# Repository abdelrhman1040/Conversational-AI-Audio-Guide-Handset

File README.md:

# Conversational-AI-Audio-Guide-Handset

ESP32-C5-based handset for a museum AI audio guide. Captures and cleans visitor speech, streams it over Wi-Fi to an edge AI server, and plays back the synthesized reply.

## Highlights

- ESP32-C5 compute/connectivity platform dual-band (2.4/5 GHz) Wi-Fi 6.
- Codec-integrated DSP for echo cancellation, noise suppression, and VAD.
- Dual-input charging: Auto-arbitrated dual-input charging (Pogo pins + USB-C).
- 12-hour runtime on a single 1S Li-Po cell.
- BOM cost-modeled for 50, 100, and 500 units.
- AI inference is handled entirely by the edge server.

## Schematic & PCB

### Schematics

*Page 1: Top-Level Hierarchy.*

*Page 2: Power & Battery Management.*

*Page 3: Microcontroller & User Interface.*

*Page 4: Audio System.*

---

### PCB Layout

## Power Subsystem

| Component | Role |
|---|---|
| AO3401A | Reverse-polarity protection (Pogo pins) |
| TPS2116DRL |2:1 auto power mux (Pogo / USB-C) |
| BQ25601 | NVDC Li-Po charger (I2C, NTC, Ship-mode) |
| TPS63001 | 3.3V buck-boost regulator |

**Battery sizing:** Sized to a 1.8–2.0 Ah cell to meet a 12-hour runtime target. Average Load: ~110–135 mA (calculated across idle, listening, playback, and Wi-Fi roaming states).  Design Margins: 92% usable DoD and 80% EOL ageing margin.  Recharge: ~0.6–0.8 A for a 3–3.5 hour full charge.

## Audio Subsystem

- **Codec:** Stereo audio codec with an embedded miniDSP. Handles AEC, noise suppression, and VAD on-chip to offload the ESP32-C5 (whose RISC-V core lacks DSP extensions).
- **Microphones:** Dual digital MEMS array (main PCB + satellite PCB). Feeds a shared digital mic bus to provide a spatial reference for far-field noise cancellation. 
- **Amplifier:** Class-D amplifier driving a single 8Ω earpiece at 88–94 dB SPL. Meets hearing-aid-compatibility (HAC) targets.
  
## UI: Status LEDs & Buttons

- **LED Driver:** 8 indicator LEDs (4 battery, 4 status) are driven via a single shift register using only 3 MCU GPIOs (Data/Clock/Latch).
- **Battery UI:** Rear LEDs indicate charge level and active charging status. They remain off to save power and are woken on-demand via a dedicated push-button.
- **Volume Controls:** Multiplexed onto a single ADC input using a resistor-divider network, resolving up/down presses via distinct voltage bands.

## Manufacturing

A preliminary Bill of Materials cost analysis was prepared at 50, 100, and 500-unit production volumes.
## Key Components

| Subsystem | Part |
|---|---|
| MCU / connectivity | ESP32-C5 |
| Audio codec / DSP | TLV320AIC3254 |
| Audio amplifier | TPA2012D2 |
| Battery charger | BQ25601 |
| Power mux | TPS2116DRL |
| Buck-boost regulator | TPS63001 |
| Reverse-polarity protection | AO3401A |
| LED driver | 74HC595 shift register |

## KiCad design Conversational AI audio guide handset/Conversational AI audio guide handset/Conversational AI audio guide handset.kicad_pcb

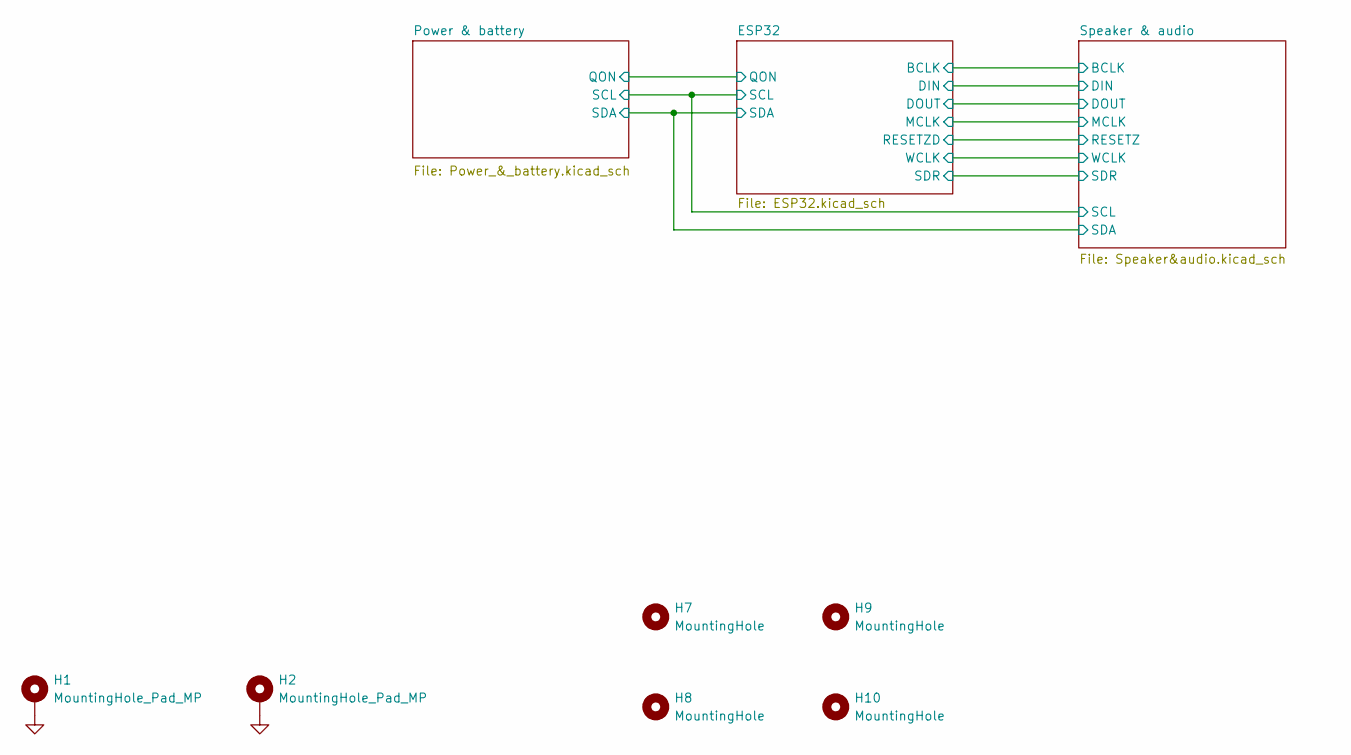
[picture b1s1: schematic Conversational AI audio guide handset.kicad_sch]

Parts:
H1, H2: MountingHole_Pad_MP; MountingHole_2.2mm_M2_Pad_Via
H7, H8, H9, H10: MountingHole; MountingHole_2.2mm_M2

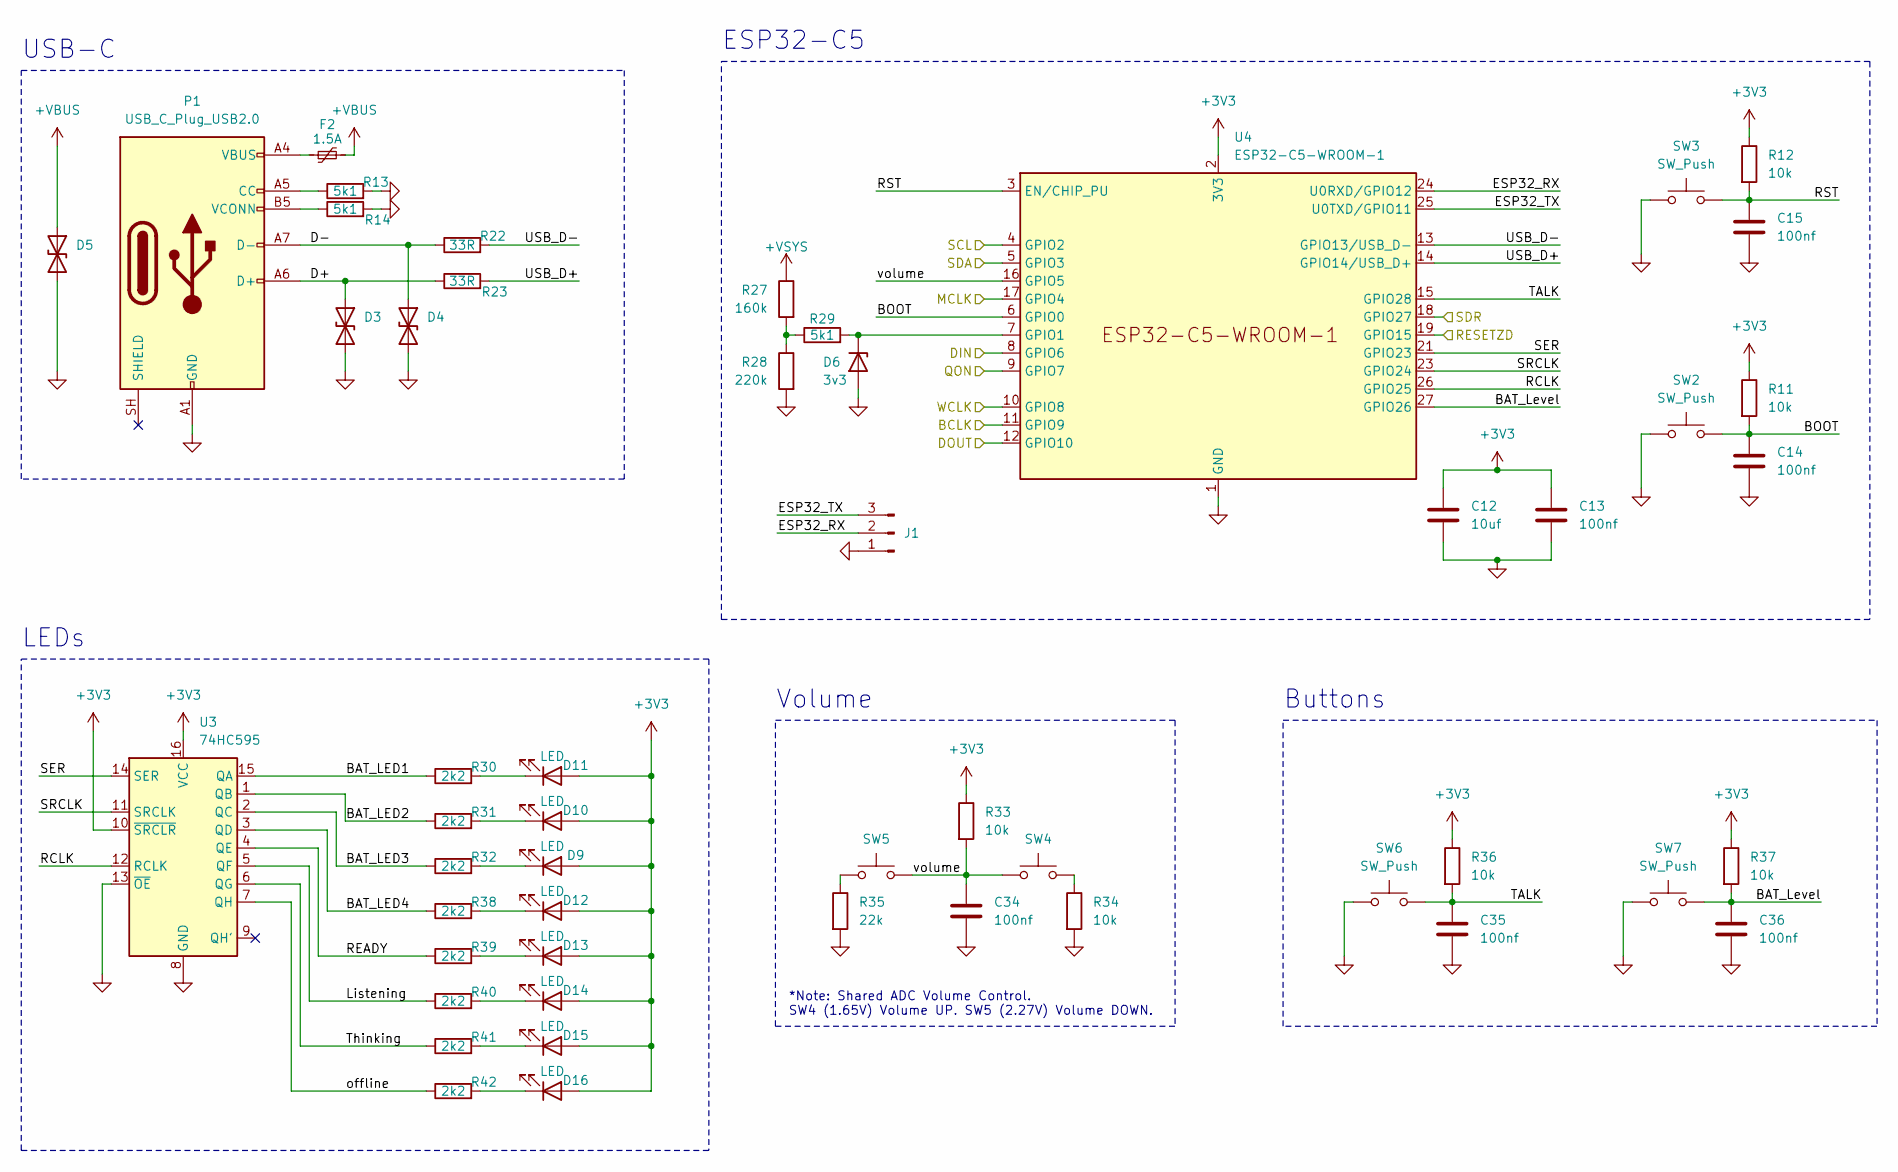
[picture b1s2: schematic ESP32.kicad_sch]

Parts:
C12: 10uf; C_0402_1005Metric
C13, C14, C15, C34, C35, C36: 100nf; C_0402_1005Metric
D3, D4, D5: LRC LESD5D5.0CT1G; D_SOD-523
D6: 3v3; D_0402_1005Metric
D9, D10, D11, D12, D13, D14, D15, D16: LED; LED_0402_1005Metric
F2: 1.5A; Fuse_1206_3216Metric
J1: Conn_01x03_Pin; PinHeader_1x03_P1.27mm_Vertical
P1: USB_C_Plug_USB2.0; USB_C_Receptacle_G-Switch_GT-USB-7010ASV
R11, R12, R33, R34, R36, R37: 10k; R_0402_1005Metric
R13, R14, R29: 5k1; R_0402_1005Metric
R22, R23: 33R; R_0402_1005Metric
R27: 160k; R_0402_1005Metric
R28: 220k; R_0402_1005Metric
R30, R31, R32, R38, R39, R40, R41, R42: 2k2; R_0402_1005Metric
R35: 22k; R_0402_1005Metric
SW2, SW3: SW_Push; SW_SPST_TS-1088-xR025
SW4, SW5, SW6, SW7: SW_Push; SW_SPST_EVQP7A
U3: 74HC595; TSSOP-16_4.4x5mm_P0.65mm
U4: ESP32-C5-WROOM-1

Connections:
+3V3: C12.1, C13.1, D9.2 (A), D10.2 (A), D11.2 (A), D12.2 (A), D13.2 (A), D14.2 (A), D15.2 (A), D16.2 (A), R11.1, R12.1, R33.1, R36.1, R37.1, U3.10 (~SRCLR), U3.16 (VCC), U4.2 (3V3); also elsewhere on the board
+VBUS: D5.1 (A1), F2.2; also elsewhere on the board
+VSYS: R27.1; also elsewhere on the board
/ESP32/BAT_LED1: R30.1, U3.15 (QA)
/ESP32/BAT_LED2: R31.1, U3.1 (QB)
/ESP32/BAT_LED3: R32.1, U3.2 (QC)
/ESP32/BAT_LED4: R38.1, U3.3 (QD)
/ESP32/BAT_Level: C36.1, R37.2, SW7.2, U4.27 (GPIO26)
/ESP32/BCLK: U4.11 (GPIO9); also elsewhere on the board
/ESP32/BOOT: C14.1, R11.2, SW2.2, U4.6 (GPIO0)
/ESP32/D+: D3.1 (A1), P1.A6 (D+), R23.1
/ESP32/D-: D4.1 (A1), P1.A7 (D-), R22.1
/ESP32/DIN: U4.8 (GPIO6); also elsewhere on the board
/ESP32/DOUT: U4.12 (GPIO10); also elsewhere on the board
/ESP32/ESP32_RX: J1.2, U4.24 (U0RXD/GPIO12)
/ESP32/ESP32_TX: J1.3, U4.25 (U0TXD/GPIO11)
/ESP32/Listening: R40.1, U3.5 (QF)
/ESP32/MCLK: U4.17 (GPIO4); also elsewhere on the board
/ESP32/QON: U4.9 (GPIO7); also elsewhere on the board
/ESP32/RCLK: U3.12 (RCLK), U4.26 (GPIO25)
/ESP32/READY: R39.1, U3.4 (QE)
/ESP32/RESETZD: U4.19 (GPIO15); also elsewhere on the board
/ESP32/RST: C15.1, R12.2, SW3.2, U4.3 (EN/CHIP_PU)
/ESP32/SCL: U4.4 (GPIO2); also elsewhere on the board
/ESP32/SDA: U4.5 (GPIO3); also elsewhere on the board
/ESP32/SDR: U4.18 (GPIO27); also elsewhere on the board
/ESP32/SER: U3.14 (SER), U4.21 (GPIO23)
/ESP32/SRCLK: U3.11 (SRCLK), U4.23 (GPIO24)
/ESP32/TALK: C35.1, R36.2, SW6.2, U4.15 (GPIO28)
/ESP32/Thinking: R41.1, U3.6 (QG)
/ESP32/USB_D+: R23.2, U4.14 (GPIO14/USB_D+)
/ESP32/USB_D-: R22.2, U4.13 (GPIO13/USB_D-)
/ESP32/WCLK: U4.10 (GPIO8); also elsewhere on the board
/ESP32/offline: R42.1, U3.7 (QH)
/ESP32/volume: C34.1, R33.2, SW4.2, SW5.2, U4.16 (GPIO5)
GND: C12.2, C13.2, C14.2, C15.2, C34.2, C35.2, C36.2, D3.2 (A2), D4.2 (A2), D5.2 (A2), D6.2 (A), J1.1, P1.A1 (GND), P1.A12 (GND), P1.B1 (GND), P1.B12 (GND), R13.2, R14.2, R28.2, R34.2, R35.2, SW2.1, SW3.1, SW6.1, SW7.1, U3.8 (GND), U3.13 (~OE), U4.1 (GND), U4.28 (GND), U4.29 (GND); also elsewhere on the board
unnamed: D6.1 (K), R29.2, U4.7 (GPIO1)
unnamed: D9.1 (K), R32.2
unnamed: D10.1 (K), R31.2
unnamed: D11.1 (K), R30.2
unnamed: D12.1 (K), R38.2
unnamed: D13.1 (K), R39.2
unnamed: D14.1 (K), R40.2
unnamed: D15.1 (K), R41.2
unnamed: D16.1 (K), R42.2
unnamed: F2.1, P1.A4 (VBUS), P1.A9 (VBUS), P1.B4 (VBUS), P1.B9 (VBUS)
unnamed: P1.A5 (CC), R13.1
unnamed: P1.B5 (VCONN), R14.1
unnamed: R27.2, R28.1, R29.1
unnamed: R34.1, SW4.1
unnamed: R35.1, SW5.1

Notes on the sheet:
Buttons
USB-C
*Note: Shared ADC Volume Control. SW4 (1.65V) Volume UP. SW5 (2.27V) Volume DOWN.
ESP32-C5
Volume
LEDs

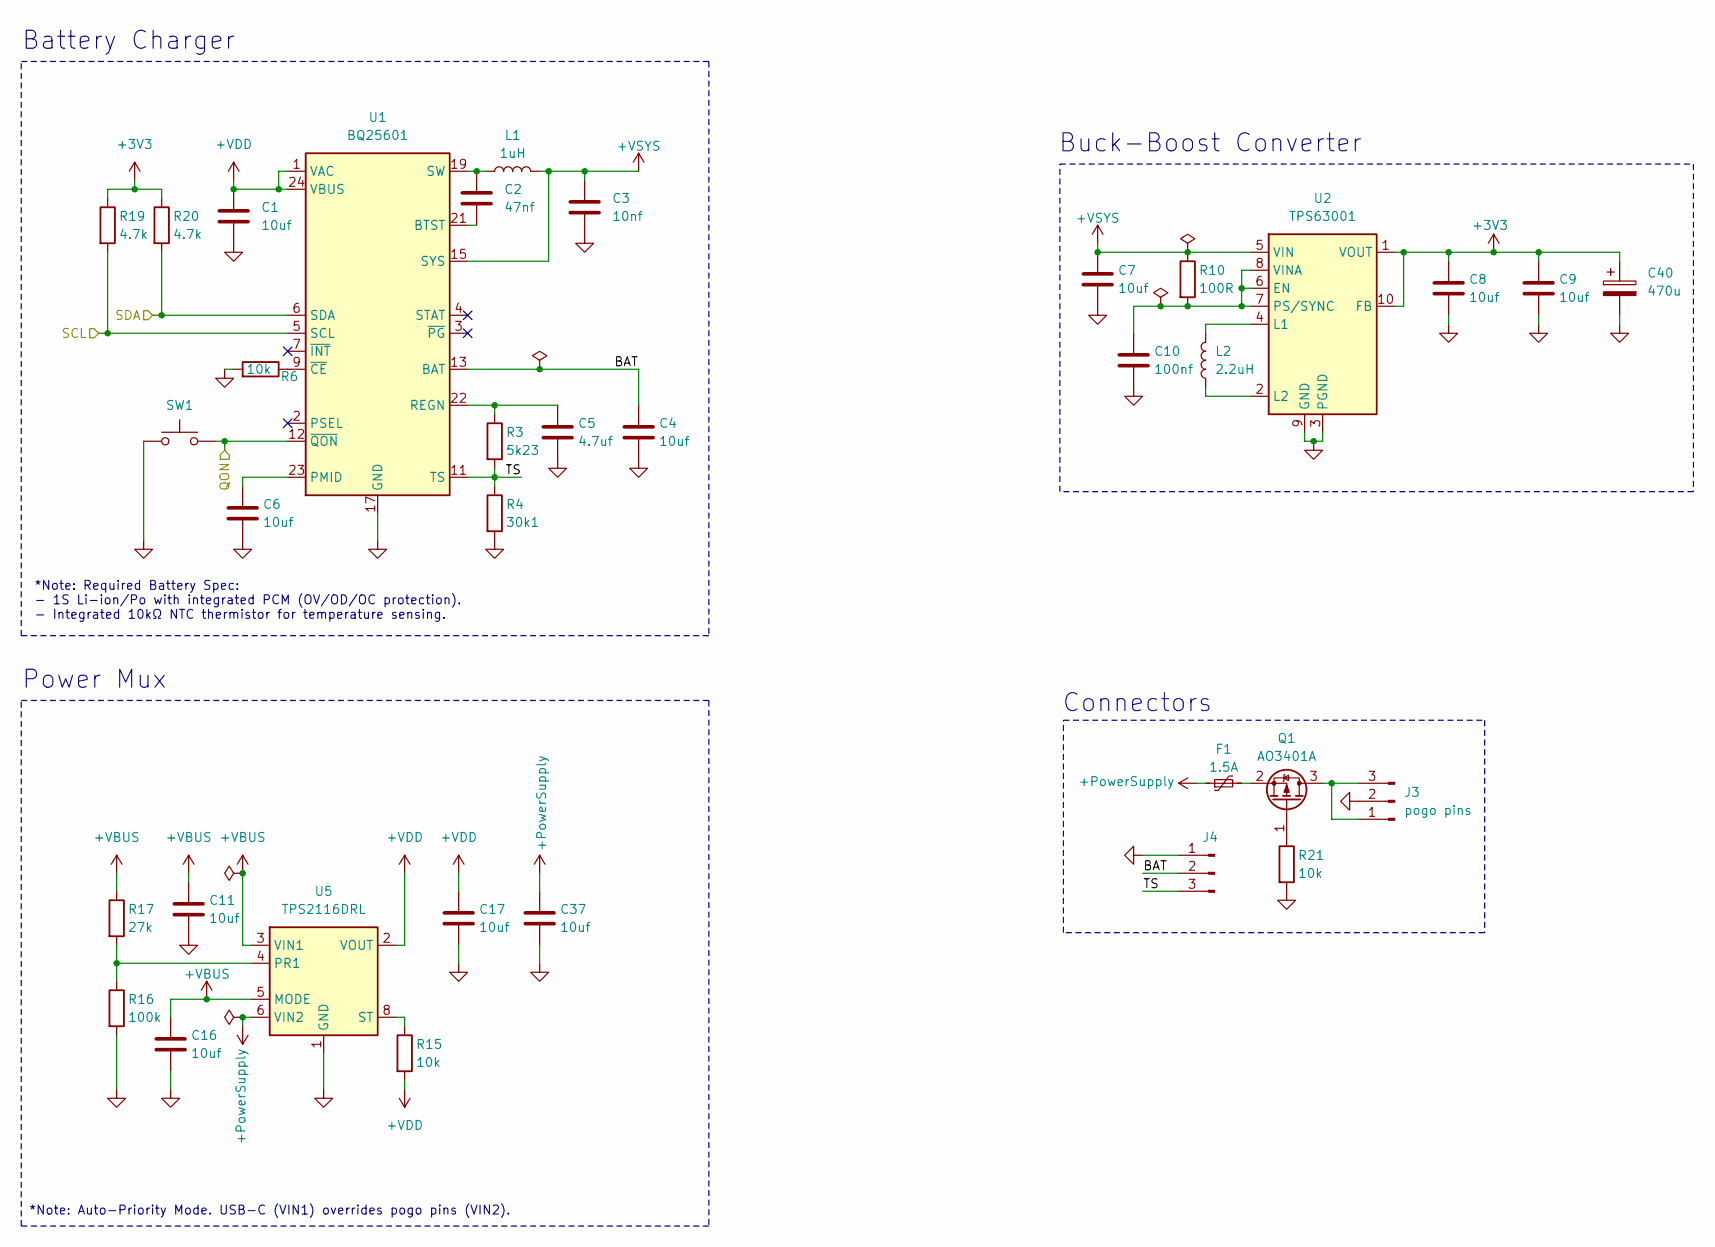
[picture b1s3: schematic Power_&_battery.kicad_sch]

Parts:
C1, C4, C7, C8, C9: 10uf; C_0805_2012Metric
C2: 47nf; C_0402_1005Metric
C3: 10nf; C_0805_2012Metric
C5: 4.7uf; C_0402_1005Metric
C6, C16: 10uf; C_0402_1005Metric
C10: 100nf; C_0402_1005Metric
C11, C17, C37: 10uf; C_0603_1608Metric
C40: 470u; CP_EIA-3216-10_Kemet-I
F1: 1.5A; Fuse_1206_3216Metric
J3: pogo pins; JST_ZH_B3B-ZR-SM4-TF_1x03-1MP_P1.50mm_Vertical
J4: Conn_01x03_Pin; JST_ZH_B3B-ZR-SM4-TF_1x03-1MP_P1.50mm_Vertical
L1: 1uH; L_Wurth_WE-LQSH-2512
L2: 2.2uH; L_Wurth_WE-LQSH-2512
Q1: AO3401A; SOT-23
R3: 5k23; R_0402_1005Metric
R4: 30k1; R_0402_1005Metric
R6, R15, R21: 10k; R_0402_1005Metric
R10: 100R; R_0402_1005Metric
R16: 100k; R_0402_1005Metric
R17: 27k; R_0402_1005Metric
R19, R20: 4.7k; R_0402_1005Metric
SW1: SW_Push; SW_SPST_EVQP7A
U1: BQ25601; Texas_RTW_WQFN-24-1EP_4x4mm_P0.5mm_EP2.7x2.7mm_ThermalVias
U2: TPS63001; Texas_DRC0010J_ThermalVias
U5: TPS2116DRL; SOT-583-8

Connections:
+3V3: C8.1, C9.1, C40.1, R19.1, R20.1, U2.1 (VOUT), U2.10 (FB); also elsewhere on the board
+PowerSupply: C37.1, F1.1, U5.6 (VIN2)
+VBUS: C11.1, C16.1, R17.1, U5.3 (VIN1), U5.5 (MODE); also elsewhere on the board
+VDD: C1.1, C17.1, R15.2, U1.1 (VAC), U1.24 (VBUS), U5.2 (VOUT), U5.7 (VOUT)
+VSYS: C3.1, C7.1, L1.2, R10.1, U1.15 (SYS), U1.16 (SYS), U2.5 (VIN); also elsewhere on the board
/ESP32/QON: SW1.2, U1.12 (~QON); also elsewhere on the board
/ESP32/SCL: R19.2, U1.5 (SCL); also elsewhere on the board
/ESP32/SDA: R20.2, U1.6 (SDA); also elsewhere on the board
/Power & battery/BAT: C4.1, J4.2, U1.13 (BAT), U1.14 (BAT)
/Power & battery/TS: J4.3, R3.2, R4.1, U1.11 (TS)
GND: C1.2, C3.2, C4.2, C5.2, C6.2, C7.2, C8.2, C9.2, C10.2, C11.2, C16.2, C17.2, C37.2, C40.2, J3.2, J4.1, R4.2, R6.2, R16.2, R21.2, SW1.1, U1.17 (GND), U1.18 (GND), U1.25 (GND), U2.3 (PGND), U2.9 (GND), U2.11 (PGND), U5.1 (GND); also elsewhere on the board
unnamed: C2.1, L1.1, U1.19 (SW), U1.20 (SW)
unnamed: J3.1, J3.3, Q1.3 (D)
unnamed: Q1.1 (G), R21.1
unnamed: F1.2, Q1.2 (S)
unnamed: C2.2, U1.21 (BTST)
unnamed: C6.1, U1.23 (PMID)
unnamed: C5.1, R3.1, U1.22 (REGN)
unnamed: R6.1, U1.9 (~CE)
unnamed: C10.1, R10.2, U2.6 (EN), U2.7 (PS/SYNC), U2.8 (VINA)
unnamed: L2.2, U2.4 (L1)
unnamed: L2.1, U2.2 (L2)
unnamed: R16.1, R17.2, U5.4 (PR1)
unnamed: R15.1, U5.8 (ST)

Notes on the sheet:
*Note: Auto-Priority Mode. USB-C (VIN1) overrides pogo pins (VIN2).
Connectors
Power Mux
*Note: Required Battery Spec: - 1S Li-ion/Po with integrated PCM (OV/OD/OC protection). - Integrated 10kΩ NTC thermistor for temperature sensing.
Buck-Boost Converter
Battery Charger

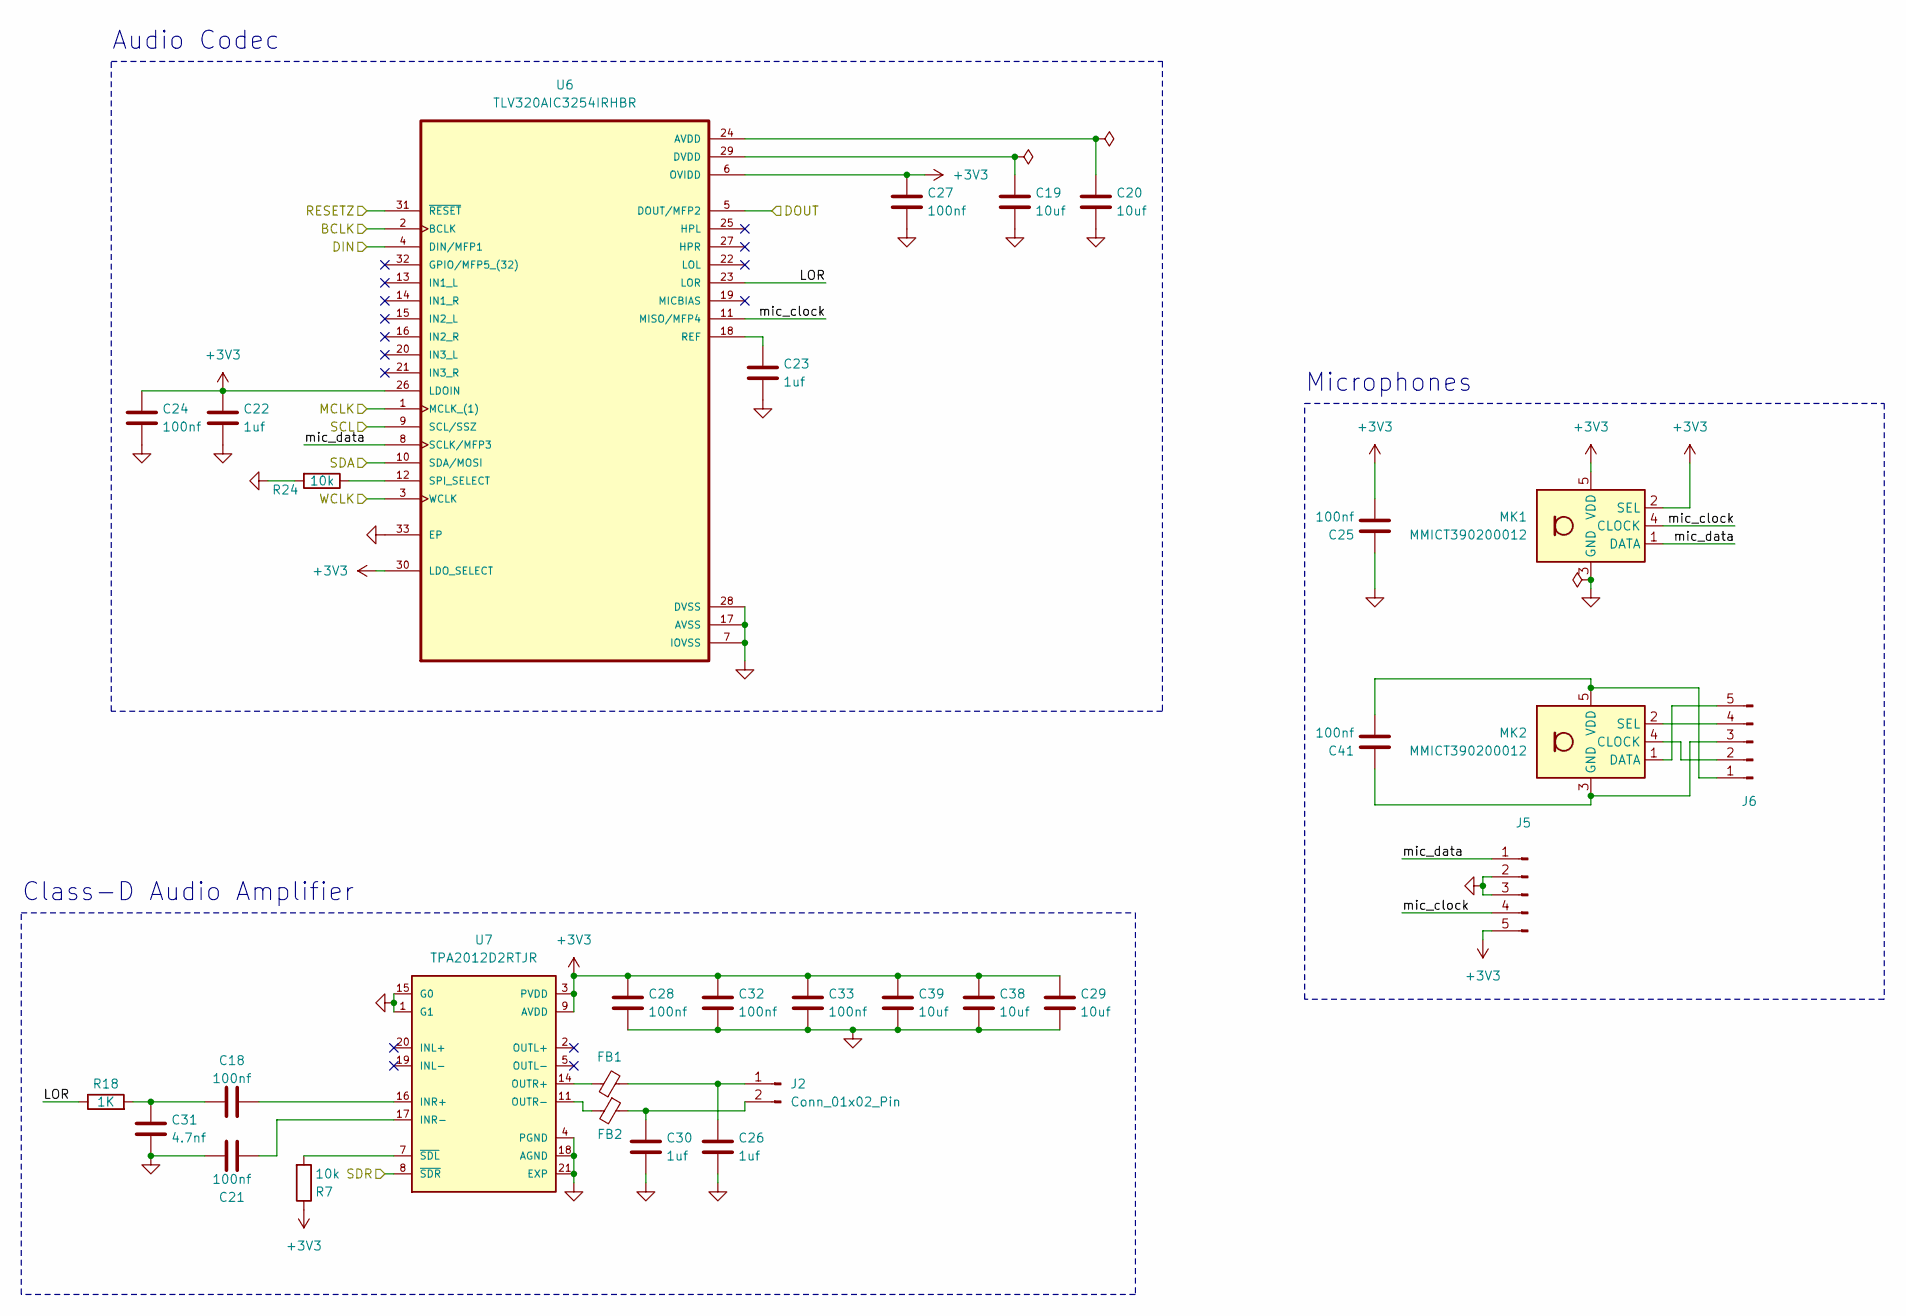
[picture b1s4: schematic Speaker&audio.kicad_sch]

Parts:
C18, C21, C24, C25, C27, C28, C32, C33, C41: 100nf; C_0402_1005Metric
C19, C20: 10uf; C_0402_1005Metric
C22, C23, C26, C30: 1uf; C_0402_1005Metric
C29, C38, C39: 10uf; C_0805_2012Metric
C31: 4.7nf; C_0402_1005Metric
FB1, FB2: FerriteBead_Small; L_0402_1005Metric
J2: Conn_01x02_Pin; JST_ZH_B2B-ZR-SM4-TF_1x02-1MP_P1.50mm_Vertical
J5, J6: Conn_01x05_Pin; JUSHUO_AFA07-S05FCA-00_1x5-1MP_P1.0mm_Horizontal
MK1, MK2: MMICT390200012; Knowles_LGA-5_3.5x2.65mm
R7, R24: 10k; R_0402_1005Metric
R18: 1K; R_0402_1005Metric
U6: TLV320AIC3254IRHBR; IC_ADS125H01IRHBT
U7: TPA2012D2RTJR; QFN50P400X400X80-21N270X270; PARTREV NA

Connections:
+3V3: C22.1, C24.1, C25.2, C27.1, C28.1, C29.1, C32.1, C33.1, C38.1, C39.1, J5.5, MK1.2 (SEL), MK1.5 (VDD), R7.1, U6.6 (OVIDD), U6.26 (LDOIN), U6.30 (LDO_SELECT), U7.3 (PVDD), U7.9 (AVDD), U7.13 (PVDD); also elsewhere on the board
/ESP32/BCLK: U6.2 (BCLK); also elsewhere on the board
/ESP32/DIN: U6.4 (DIN/MFP1); also elsewhere on the board
/ESP32/DOUT: U6.5 (DOUT/MFP2); also elsewhere on the board
/ESP32/MCLK: U6.1 (MCLK_(1)); also elsewhere on the board
/ESP32/RESETZD: U6.31 (~RESET); also elsewhere on the board
/ESP32/SCL: U6.9 (SCL/SSZ); also elsewhere on the board
/ESP32/SDA: U6.10 (SDA/MOSI); also elsewhere on the board
/ESP32/SDR: U7.8 (~SDR); also elsewhere on the board
/ESP32/WCLK: U6.3 (WCLK); also elsewhere on the board
/Speaker & audio/LOR: R18.1, U6.23 (LOR)
/Speaker & audio/mic_clock: J5.4, MK1.4 (CLOCK), U6.11 (MISO/MFP4)
/Speaker & audio/mic_data: J5.1, MK1.1 (DATA), U6.8 (SCLK/MFP3)
GND: C19.2, C20.2, C21.2, C22.2, C23.2, C24.2, C25.1, C26.2, C27.2, C28.2, C29.2, C30.2, C31.2, C32.2, C33.2, C38.2, C39.2, J5.2, J5.3, MK1.3 (GND), R24.2, U6.7 (IOVSS), U6.17 (AVSS), U6.28 (DVSS), U6.33 (EP), U7.1 (G1), U7.4 (PGND), U7.12 (PGND), U7.15 (G0), U7.18 (AGND), U7.21 (EXP); also elsewhere on the board
unnamed: C18.1, C31.1, R18.2
unnamed: C26.1, FB1.2, J2.1
unnamed: C30.1, FB2.1, J2.2
unnamed: C41.2, J6.1, MK2.5 (VDD)
unnamed: J6.2, MK2.4 (CLOCK)
unnamed: C41.1, J6.3, MK2.3 (GND)
unnamed: J6.4, MK2.2 (SEL)
unnamed: J6.5, MK2.1 (DATA)
unnamed: C20.1, U6.24 (AVDD)
unnamed: C19.1, U6.29 (DVDD)
unnamed: C23.1, U6.18 (REF)
unnamed: R24.1, U6.12 (SPI_SELECT)
unnamed: C18.2, U7.16 (INR+)
unnamed: C21.1, U7.17 (INR-)
unnamed: FB1.1, U7.14 (OUTR+)
unnamed: FB2.2, U7.11 (OUTR-)
unnamed: R7.2, U7.7 (~SDL)

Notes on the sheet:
Microphones
Audio Codec
Class-D Audio Amplifier

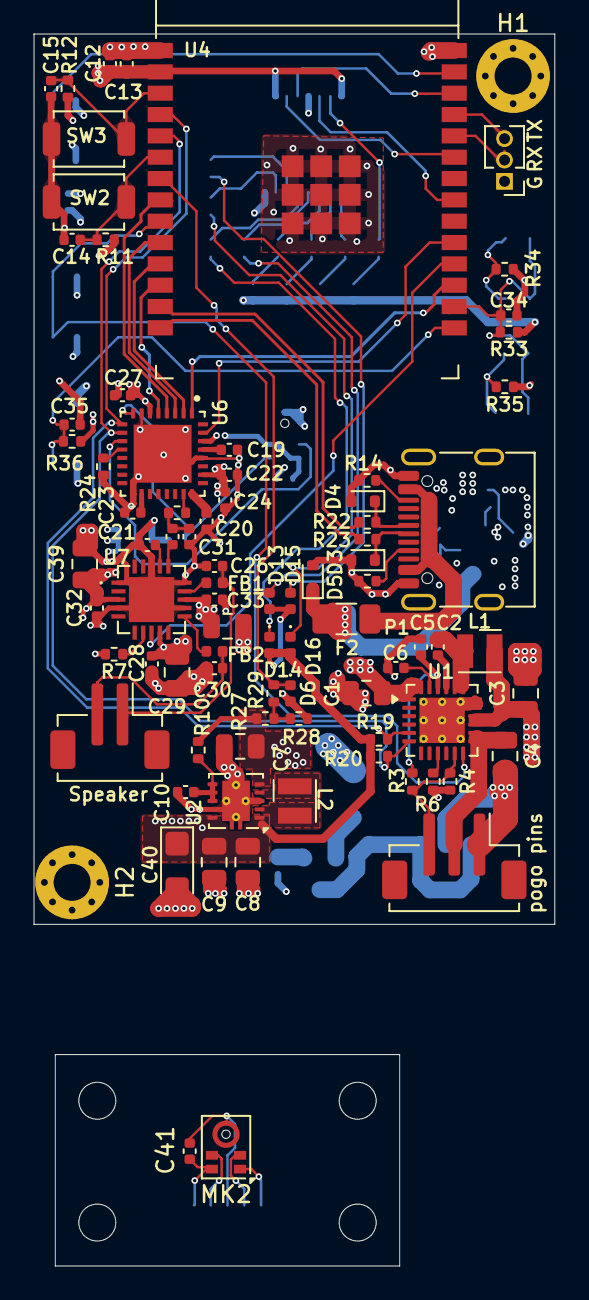
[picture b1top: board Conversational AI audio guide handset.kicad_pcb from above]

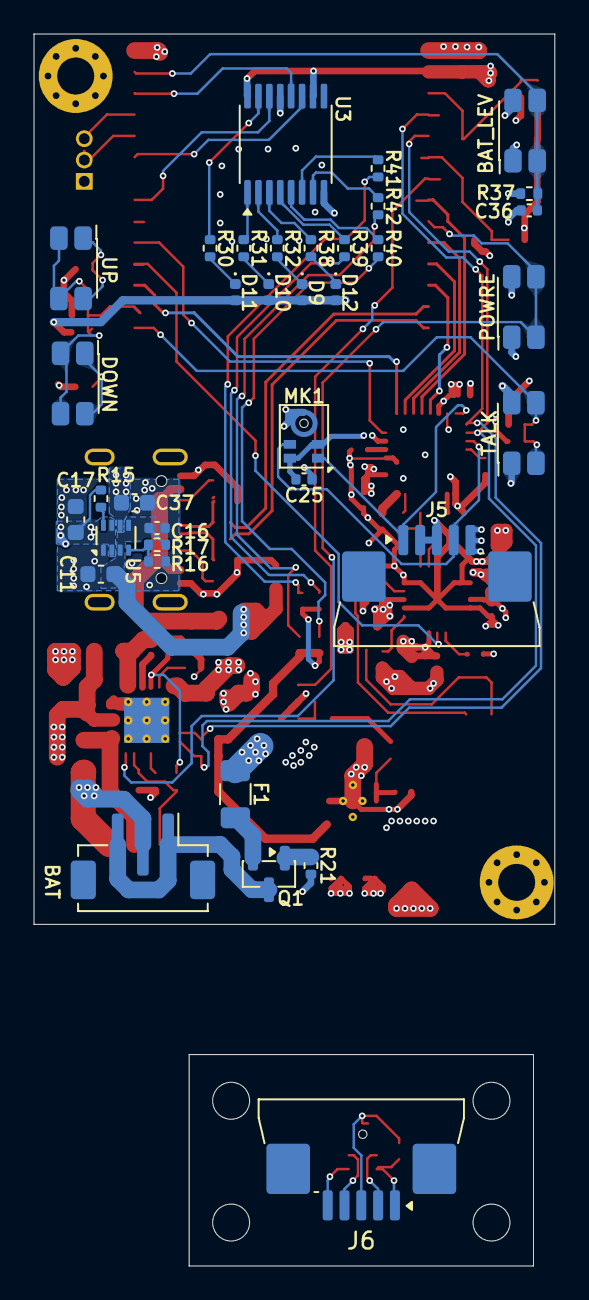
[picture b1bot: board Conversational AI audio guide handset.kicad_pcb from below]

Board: 4 copper layers, 31.0 x 53.0 mm, 124 parts (36 on the bottom side), 88 nets.

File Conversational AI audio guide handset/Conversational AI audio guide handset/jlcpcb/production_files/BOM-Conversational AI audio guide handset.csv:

Comment,Designator,Footprint,LCSC,Quantity
1.5A,"F1,F2",Fuse_1206_3216Metric,C16902,2
100R,R10,R_0402_1005Metric,C82865,1
100k,R16,R_0402_1005Metric,C25741,1
100nf,"C10,C13,C14,C15,C18,C21,C24,C25,C27,C28,C32,C33,C34,C35,C36",C_0402_1005Metric,C1525,15
10k,R7,R_0402_1005Metric,C11616,1
10k,"R11,R12,R15,R21,R24,R33,R34,R36,R37,R6",R_0402_1005Metric,C2906861,10
10nf,C3,C_0805_2012Metric,C519909,1
10uf,"C1,C29,C38,C39,C4,C7,C8,C9",C_0805_2012Metric,C1713,8
10uf,"C11,C17,C37",C_0603_1608Metric,C19702,3
10uf,"C12,C16,C19,C20,C6",C_0402_1005Metric,C7472949,5
160k,R27,R_0402_1005Metric,C25757,1
1K,R18,R_0402_1005Metric,C71623,1
1uH,L1,L_Wurth_WE-LQSH-2512,C340349,1
1uf,"C22,C23,C26,C30",C_0402_1005Metric,C14445,4
2.2uH,L2,L_Wurth_WE-LQSH-2512,C7471167,1
220k,R28,R_0402_1005Metric,C25546,1
22k,R35,R_0402_1005Metric,C82868,1
27k,R17,R_0402_1005Metric,C137891,1
2k2,"R30,R31,R32,R38,R39,R40,R41,R42",R_0402_1005Metric,C140192,8
30k1,R4,R_0402_1005Metric,C138009,1
33R,"R22,R23",R_0402_1005Metric,C324773,2
3v3,D6,D_0402_1005Metric,C550402,1
4.7k,"R19,R20",R_0402_1005Metric,C11663,2
4.7nf,C31,C_0402_1005Metric,C2168463,1
4.7uf,C5,C_0402_1005Metric,C368809,1
470u,C40,CP_EIA-3216-10_Kemet-I,C7229,1
47nf,C2,C_0402_1005Metric,C327054,1
5k1,"R13,R14,R29",R_0402_1005Metric,C105872,3
5k23,R3,R_0402_1005Metric,C477746,1
74HC595,U3,TSSOP-16_4.4x5mm_P0.65mm,C5948,1
AO3401A,Q1,SOT-23,C15127,1
BQ25601,U1,Texas_RTW_WQFN-24-1EP_4x4mm_P0.5mm_EP2.7x2.7mm_ThermalVias,C468236,1
Conn_01x02_Pin,J2,JST_ZH_B2B-ZR-SM4-TF_1x02-1MP_P1.50mm_Vertical,C265004,1
Conn_01x03_Pin,J4,JST_ZH_B3B-ZR-SM4-TF_1x03-1MP_P1.50mm_Vertical,C489717,1
Conn_01x03_Pin,J1,PinHeader_1x03_P1.27mm_Vertical,C52016391,1
Conn_01x05_Pin,J5,JUSHUO_AFA07-S05FCA-00_1x5-1MP_P1.0mm_Horizontal,C2681941,1
ESP32-C5-WROOM-1,U4,ESP32-C5-WROOM-1,C51950748,1
FerriteBead_Small,"FB1,FB2",L_0402_1005Metric,C76807,2
LED,"D10,D11,D12,D13,D14,D15,D16,D9",LED_0402_1005Metric,C74339,8
LRC LESD5D5.0CT1G,"D3,D4,D5",D_SOD-523,C5274290,3
SPH0641LU4H-1,MK1,Knowles_LGA-5_3.5x2.65mm,C3171752,1
SW_Push,"SW2,SW3",SW_SPST_TS-1088-xR025,C720477,2
SW_Push,"SW1,SW4,SW5,SW6,SW7",SW_SPST_EVQP7A,C79167,5
TLV320AIC3254IRHBR,U6,IC_ADS125H01IRHBT,C9925,1
TPA2012D2RTJR,U7,QFN50P400X400X80-21N270X270,C7717,1
TPS2116DRL,U5,SOT-583-8,C3235557,1
TPS63001,U2,Texas_DRC0010J_ThermalVias,C28060,1
USB_C_Plug_USB2.0,P1,USB_C_Receptacle_G-Switch_GT-USB-7010ASV,C393939,1
pogo pins,J3,JST_ZH_B3B-ZR-SM4-TF_1x03-1MP_P1.50mm_Vertical,C489717,1
